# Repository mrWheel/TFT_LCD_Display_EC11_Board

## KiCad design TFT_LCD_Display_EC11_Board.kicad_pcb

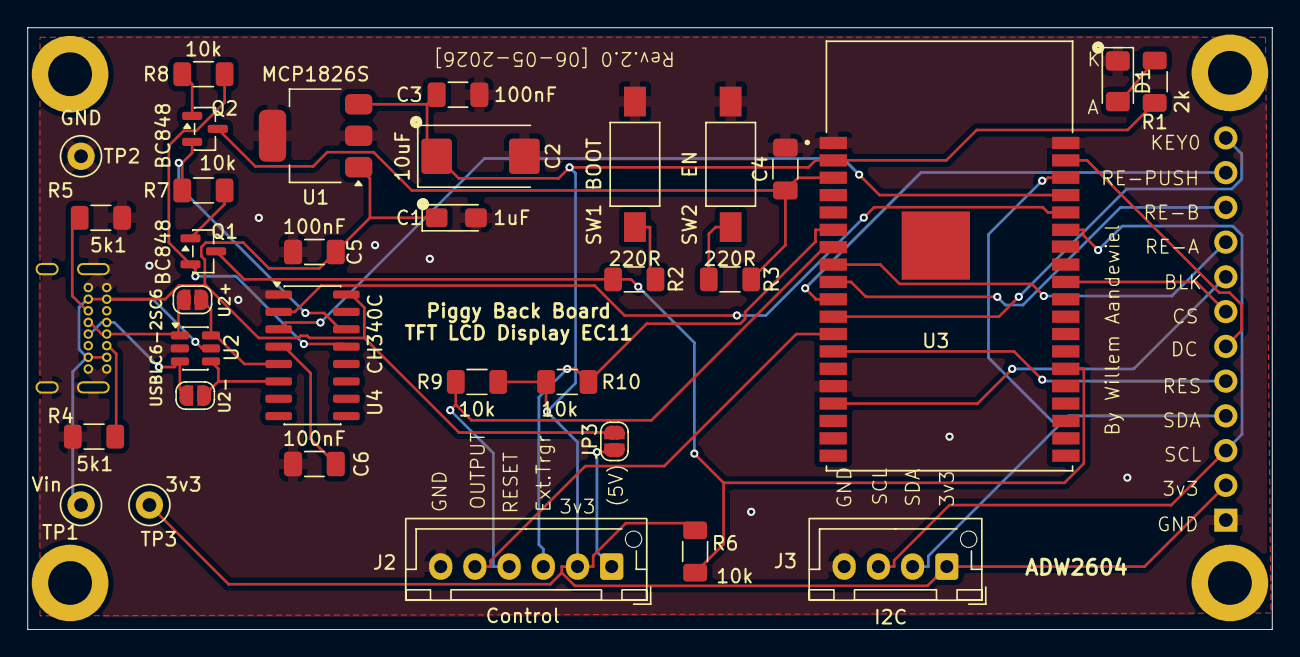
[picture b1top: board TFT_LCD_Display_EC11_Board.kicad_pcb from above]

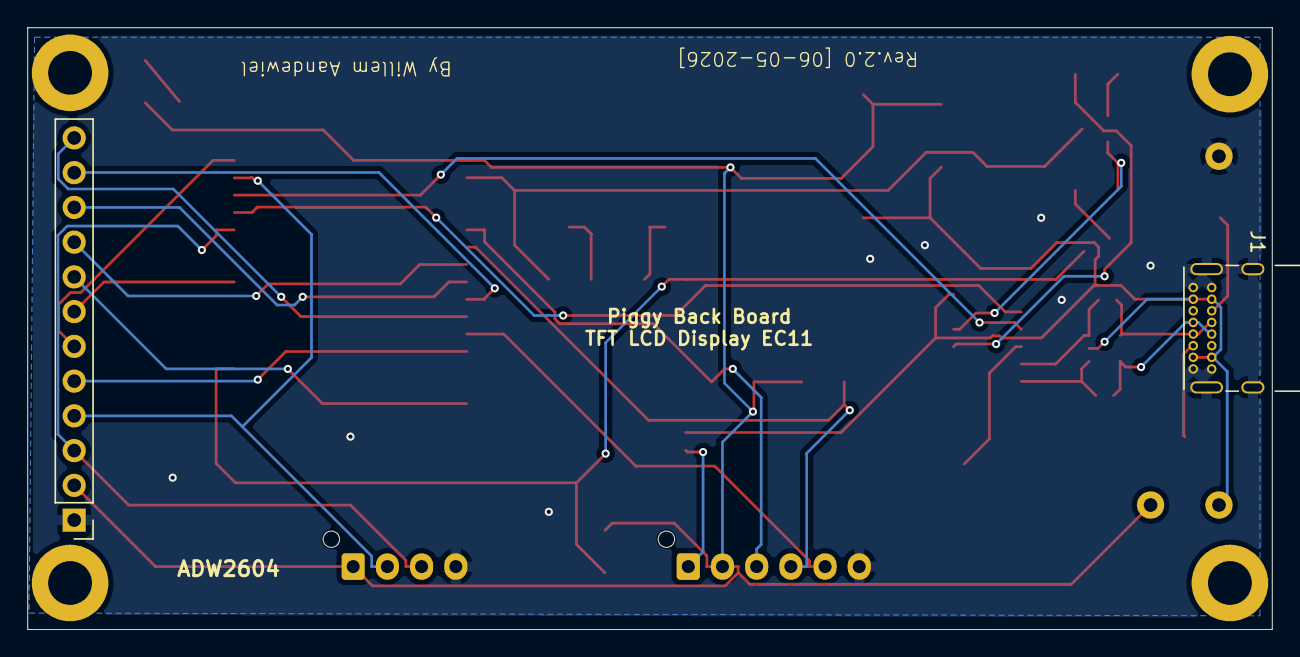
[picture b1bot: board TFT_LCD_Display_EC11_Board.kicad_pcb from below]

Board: 2 copper layers, 91.0 x 44.0 mm, 39 parts (2 on the bottom side), 35 nets.

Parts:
C1: 1uF; CP_EIA-3216-12_Kemet-S_HandSolder
C2: 10uF; CP_EIA-7343-31_Kemet-D_HandSolder
C3, C4, C5, C6: 100nF; C_1206_3216Metric_Pad1.33x1.80mm_HandSolder
D1: 3v3; LED_1206_3216Metric_Pad1.42x1.75mm_HandSolder
H1, H2, H3, H4: MountingHole; MountingHole_3.2mm_M3_DIN965_Pad
J1: USB_C_Receptacle_USB2.0_16P; USB_C_Receptacle_GCT_USB4085
J2: Control; JST_XH_B6B-XH-AM_1x06_P2.50mm_Vertical
J3: I2C; JST_XH_B4B-XH-AM_1x04_P2.50mm_Vertical
J4: TFT-LCD-DISPLAY-EC11; PinHeader_1x12_P2.54mm_Vertical
JP1: U2+; SolderJumper-2_P1.3mm_Open_RoundedPad1.0x1.5mm
JP2: U2-; SolderJumper-2_P1.3mm_Open_RoundedPad1.0x1.5mm
JP3: 5Volt; SolderJumper-2_P1.3mm_Open_RoundedPad1.0x1.5mm
Q1, Q2: BC848; SOT-23
R1: 2k; R_1206_3216Metric_Pad1.30x1.75mm_HandSolder
R2, R3: 220R; R_1206_3216Metric_Pad1.30x1.75mm_HandSolder
R4, R5: 5k1; R_1206_3216Metric_Pad1.30x1.75mm_HandSolder
R6, R7, R8, R9, R10: 10k; R_1206_3216Metric_Pad1.30x1.75mm_HandSolder
SW1: BOOT; SW_SPST_FSMSM
SW2: EN; SW_SPST_FSMSM
TP1: Vin; TestPoint_Loop_D2.50mm_Drill1.0mm
TP2: GND; TestPoint_Loop_D2.50mm_Drill1.0mm
TP3: 3v3; TestPoint_Loop_D2.50mm_Drill1.0mm
U1: MCP1826S; SOT-223-3_TabPin2
U2: USBLC6-2SC6; SOT-23-6
U3: ESP32-WROVER-E-N4R8; ESP32-WROVER-B-E
U4: CH340C; SOIC-16_3.9x9.9mm_P1.27mm

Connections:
3v3: C2.1, C3.1, J2.2, J3.1, J4.2, R1.2, R6.2, R9.2, R10.2, TP3.1 (1_1), U1.3 (VO), U3.2 (3V3)
A: J4.9, U3.8 (IO32)
B: J4.10, U3.9 (IO33)
BLK: J4.8, U3.16 (IO13)
CS: J4.7, U3.30 (IO18)
D+: J1.A6 (D+), J1.B6 (D+), JP1.1 (A), U2.1 (I/O1)
D-: J1.A7 (D-), J1.B7 (D-), JP2.1 (A), U2.3 (I/O2)
DC: J4.6, U3.37 (IO23)
ESP-RX: U3.34 (RXD0), U4.2 (TXD)
ESP-TX: U3.35 (TXD0), U4.3 (RXD)
EXT-TRIGGER: J2.3, R10.1, U3.6 (IO34)
GND: C1.2, C2.2, C3.2, C4.2, C5.2, C6.2, D1.1 (K), J1.A1 (GND), J1.A12 (GND), J1.B1 (GND), J1.B12 (GND), J1.SH (SHIELD), J2.6, J3.4, J4.1, R4.2, R5.2, SW1.1, SW2.1, TP2.1 (1_1), U1.2 (GND), U2.2 (GND), U3.1 (GND), U3.15 (GND), U3.38 (GND), U4.1 (GND)
GPIO0: Q1.3 (C), R2.2, R6.1, U3.25 (IO0)
K0: J4.12, U3.11 (IO26)
unnamed: D1.2 (A), R1.1
unnamed: J1.A5 (CC1), R4.1
unnamed: J1.B5 (CC2), R5.1
unnamed: J2.1, JP3.1 (A)
unnamed: JP1.2 (B), U2.6 (I/O1), U4.5 (UD+)
unnamed: JP2.2 (B), U2.4 (I/O2), U4.6 (UD-)
unnamed: Q1.1 (B), R7.2
unnamed: Q2.1 (B), R8.2
unnamed: R2.1, SW1.2
unnamed: R3.1, SW2.2
unnamed: C6.1, U4.4 (V3)
OUTPUT: J2.5, U3.12 (IO27)
PUSH: J4.11, U3.10 (IO25)
RES: J4.5, U3.13 (IO14)
RESET: J2.4, R9.1, U3.7 (IO35)
SCL: J3.3, J4.3, U3.33 (IO21)
SDA: J3.2, J4.4, U3.36 (IO22)
VBUS: C1.1, C5.1, J1.A4 (VBUS), J1.A9 (VBUS), J1.B4 (VBUS), J1.B9 (VBUS), JP3.2 (B), TP1.1 (1_1), U1.1 (VI), U2.5 (VBUS), U4.16 (VCC)
~DTR: Q1.2 (E), R8.1, U4.13 (~DTR)
~ENABLE: C4.1, Q2.3 (C), R3.2, U3.3 (EN)
~RTS: Q2.2 (E), R7.1, U4.14 (~RTS)

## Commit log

2026-04-21 Inital Commit
2026-04-21 Tweede Commit
2026-04-23 Add 3D/openSCAD
2026-05-05 3D Files
2026-05-05 Add .DS_STORE to gitignore
2026-05-05 Added DIN ring
2026-05-06 Combine Rev 2.0 and openSCAD files
